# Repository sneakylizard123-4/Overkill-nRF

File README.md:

# Overkill nRF Board

A modular RF communication board designed for the **Overkill system**, built around the **nRF24L01+ radio module** instead of a bare RF IC + Amplifier. This makes the design easier to assemble, debug, and iterate while keeping it fully modular inside the Overkill ecosystem.

---

## Overview

The Overkill nRF Board handles wireless communication for the system using **nRF24L01+ modules**.

It is designed to be:

- Easy to assemble (no RF IC routing complexity)
- Modular (plugs into Overkill ecosystem)
- Hackable (all signals exposed)
- Repairable (no fine-pitch RF ICs)
- Hand-solderable (mostly 0805 components)

### Operating Modes

- **Standalone mode** → acts like a standard nRF24 breakout module
- **Integrated mode** → RF subsystem inside Overkill system

---

## Why

- Most off-the-shelf nRF24 setups are either too barebones or too messy to integrate into real projects. Debugging is hard, power handling is often ignored, and the RF design is usually not optimized for real-world use.
- This board is designed to be a **usable, hackable, and modular RF subsystem** that can be easily integrated into the Overkill system or used standalone for RF experimentation.

---

## Key Changes from Previous Revision

- Removed discrete nRF24 RF IC design
- Switched to **nRF24L01+ module-based design**
- Simplified RF routing significantly
- Improved reliability and build speed
- Reduced RF design complexity

---

## Hardware

### Radio

- nRF24L01+ module (SPI interface)
- Optional PA+LNA module support (with proper power handling)

### Components

- Mostly **0805 footprint components**
  - Easier soldering
  - Better availability
  - More forgiving for hand assembly

### Interface

Connection to Overkill system via **JST-PH connector**:

- 3.3V power
- Data signals

---

## Design Philosophy

This board prioritizes:

- Simplicity over compact size
- Modularity over integration
- Debuggability over RF perfection

The goal is fast iteration for RF experimentation inside the Overkill platform.

---

## Power Notes

- Requires stable **3.3V supply** or **USB power** with proper regulation
- nRF24 modules are 5V tolerant, but the esp32 is not, so 3.3V is used for the logic part of the board
- Add decoupling capacitors close to module
- PA+LNA modules may require higher current bursts during transmission, so ensure power supply can handle it

---

## PCB Design Notes

- Designed around **0805 components**
- Maintain solid ground plane under RF section
- Keep antenna area free of copper and components
- use external antennas if possible for better performance

---

## Images

All pictures and screenshots should be in the `images/` folder.

### PCB Layout

---

### 3D Renders

Top-side render (ray-traced KiCad):

Bottom-side render (ray-traced KiCad):

---

### Schematics

schematic sheet 1:

schematic sheet 2:

---

### Manufacturing / Sourcing

AliExpress cart:

LCSC sourcing carts:

JLCPCB cart:

or maybe PCBWay if they sponsor this project too!

---

### Zine Page

## System Integration

The board connects into the Overkill system via JST-PH and is designed to interface with:

- Core controller board (SPI master)
- Power distribution board
- Other modular subsystems

Other parts of the system are being developed separately.

---

## Assembly and Programming

1. Start with passives
   - Solder resistors and capacitors first
   - Double-check values and placements
2. Power section
   - Assemble regulator and power filtering stage
   - Verify 3.3V rail before adding ICs
3. MCU and logic components
   - Solder ESP32 and other chips
   - Inspect for shorts between pins
4. nRF24 module
   - Carefully align pins
   - ensure solid ground connection
5. LEDs and indicators
   - Add status LEDs if desired
   - Match polarity correctly
   - Confirm resistor values for current limiting
6. Final inspection
   - Continuity check all power rails
   - Inspect RF sections for solder bridges

---

## How to Use

1. Powering the board
   - Connect USB power or 3.3V supply to the JST-PH connector
   - Ensure power supply can provide sufficient current for nRF24 module, especially if using PA+LNA version
2. Programming the ESP32
   - Use PlatformIO or Arduino IDE to flash firmware
   - Connect to the board via USB or UART for debugging
3. Integrating with Overkill system
   - Connect the board to the core controller via JST-PH
   - Use SPI interface to communicate with the nRF24 module
   - Test RF communication with other nRF24 devices

---

## Bill of Materials (BOM)

A full BOM is included in the repository.
see [bom.csv](bom/bom.csv) for details.

It includes:

- Component references
- Values / part numbers
- Quantities
- LCSC number
- Where to get them (AliExpress, LCSC, etc.)

---

## Repository Structure

- bom/ - Bill of Materials (BOM) files
- blender/ - 3D models and renders
- cad/ - STEP files
- firmware/ - code for project (platformio)
- images/ - pictures and screenshots
- kicad/ - KiCad project files
- zine/ - zine page for hack club

---

## Status

- Breadboard Prototype complete
- PCB routed in KiCad
- 3D assembly done
- Ready for fabrication

---

## Notes

This revision prioritizes usability and fast iteration over RF optimization complexity. The goal is to make RF experimentation inside the Overkill system fast, modular, and actually enjoyable to play with.

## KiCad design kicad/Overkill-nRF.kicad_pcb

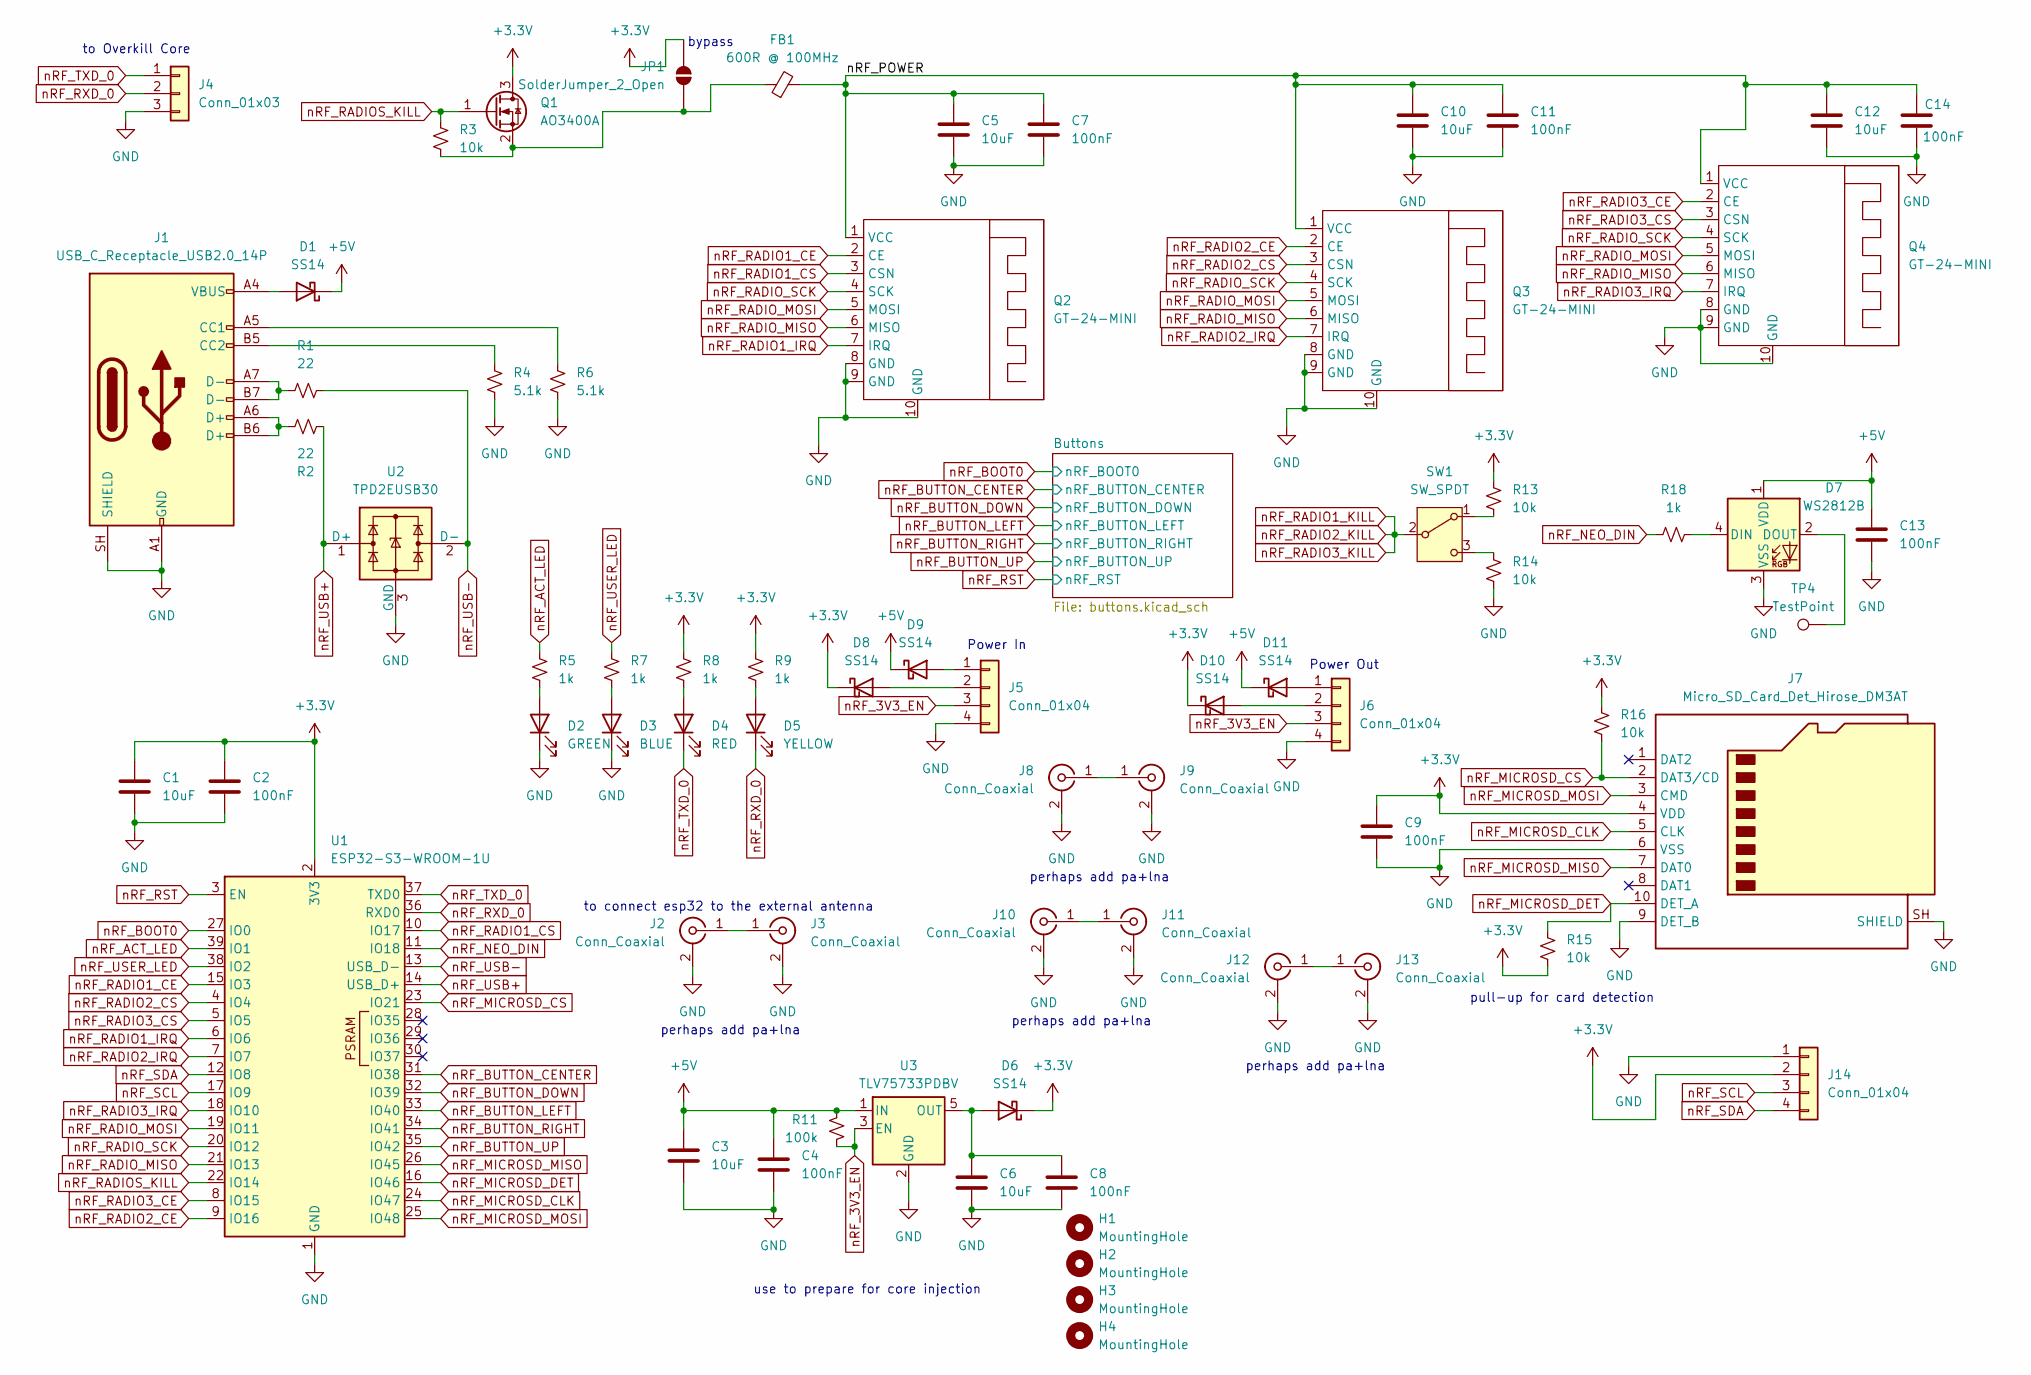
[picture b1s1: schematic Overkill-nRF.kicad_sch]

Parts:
C1, C3, C5, C6, C10, C12: 10uF; C_0805_2012Metric
C2, C4, C7, C8, C9, C11, C13, C14: 100nF; C_0805_2012Metric
D1, D6, D8, D9, D10, D11: SS14; D_SMA
D2: GREEN; LED_0805_2012Metric
D3: BLUE; LED_0805_2012Metric
D4: RED; LED_0805_2012Metric
D5: YELLOW; LED_0805_2012Metric
D7: WS2812B; LED_WS2812B_PLCC4_5.0x5.0mm_P3.2mm
FB1: 600R @ 100MHz; L_0805_2012Metric
H1, H2, H3, H4: MountingHole; MountingHole_3.2mm_M3
J1: USB_C_Receptacle_USB2.0_14P; USB_C_Receptacle_HRO_TYPE-C-31-M-12
J2, J8, J10, J12: Conn_Coaxial; U.FL_Molex_MCRF_73412-0110_Vertical
J3, J9, J11, J13: Conn_Coaxial; SMA_Amphenol_132289_EdgeMount
J4: Conn_01x03; JST_PH_S3B-PH-K_1x03_P2.00mm_Horizontal
J5, J6: Conn_01x04; JST_PH_S4B-PH-K_1x04_P2.00mm_Horizontal
J7: Micro_SD_Card_Det_Hirose_DM3AT; microSD_HC_Molex_104031-0811
J14: Conn_01x04; PinSocket_1x04_P2.54mm_Vertical
JP1: SolderJumper_2_Open; SolderJumper-2_P1.3mm_Open_RoundedPad1.0x1.5mm
Q1: AO3400A; SOT-23
Q2, Q3, Q4: GT-24-MINI; nRF24L01-GT24_Breakout
R1, R2: 22; R_0805_2012Metric
R3, R13, R14, R15, R16: 10k; R_0805_2012Metric
R4, R6: 5.1k; R_0805_2012Metric
R5, R7, R8, R9, R18: 1k; R_0805_2012Metric
R11: 100k; R_0805_2012Metric
SW1: SW_SPDT; SW_SPDT_CK_JS102011SAQN
TP4: TestPoint; TestPoint_Pad_D1.5mm
U1: ESP32-S3-WROOM-1U
U2: TPD2EUSB30; Texas_DRT-3
U3: TLV75733PDBV; SOT-23-5

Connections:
+3.3V: C1.1, C2.1, C9.1, D6.1 (K), D8.1 (K), D10.1 (K), J7.4 (VDD), J14.2, JP1.2 (B), Q1.3 (D), R8.1, R9.1, R13.1, R15.2, R16.1, U1.2 (3V3); also elsewhere on the board
+5V: C3.1, C4.1, C13.1, D1.1 (K), D7.1 (VDD), D9.1 (K), D11.1 (K), R11.1, U3.1 (IN)
/nRF_POWER: C5.1, C7.1, C10.1, C11.1, C12.1, C14.1, FB1.2, Q2.1 (VCC), Q3.1 (VCC), Q4.1 (VCC)
GND: C1.2, C2.2, C3.2, C4.2, C5.2, C6.2, C7.2, C8.2, C9.2, C10.2, C11.2, C12.2, C13.2, C14.2, D2.1 (K), D3.1 (K), D7.3 (VSS), J1.A1 (GND), J1.A12 (GND), J1.B1 (GND), J1.B12 (GND), J1.SH (SHIELD), J2.2 (Ext), J3.2 (Ext), J4.3, J5.4, J6.4, J7.6 (VSS), J7.9 (DET_B), J7.SH (SHIELD), J8.2 (Ext), J9.2 (Ext), J10.2 (Ext), J11.2 (Ext), J12.2 (Ext), J13.2 (Ext), J14.1, Q2.8 (GND), Q2.9 (GND), Q2.10 (GND), Q3.8 (GND), Q3.9 (GND), Q3.10 (GND), Q4.8 (GND), Q4.9 (GND), Q4.10 (GND), R4.2, R6.2, R14.2, U1.1 (GND), U1.40 (GND), U1.41 (GND), U2.3 (GND), U3.2 (GND); also elsewhere on the board
unnamed: D1.2 (A), J1.A4 (VBUS), J1.A9 (VBUS), J1.B4 (VBUS), J1.B9 (VBUS)
unnamed: D2.2 (A), R5.2
unnamed: D3.2 (A), R7.2
unnamed: D4.2 (A), R8.2
unnamed: D5.2 (A), R9.2
unnamed: C6.1, C8.1, D6.2 (A), U3.5 (OUT)
unnamed: D7.4 (DIN), R18.2
unnamed: D7.2 (DOUT), TP4.1 (1_1)
unnamed: D8.2 (A), J5.2
unnamed: D9.2 (A), J5.1
unnamed: D10.2 (A), J6.2
unnamed: D11.2 (A), J6.1
unnamed: J1.A5 (CC1), R6.1
unnamed: J1.B5 (CC2), R4.1
unnamed: J1.A6 (D+), J1.B6 (D+), R2.2
unnamed: J1.A7 (D-), J1.B7 (D-), R1.1
unnamed: J2.1 (In), J3.1 (In)
unnamed: J8.1 (In), J9.1 (In)
unnamed: J10.1 (In), J11.1 (In)
unnamed: J12.1 (In), J13.1 (In)
unnamed: FB1.1, JP1.1 (A), Q1.2 (S), R3.2
unnamed: R13.2, SW1.1 (A)
unnamed: R14.1, SW1.3 (C)
nRF_3V3_EN: J5.3, J6.3, R11.2, U3.3 (EN)
nRF_ACT_LED: R5.1, U1.39 (IO1)
nRF_BOOT0: U1.27 (IO0); also elsewhere on the board
nRF_BUTTON_CENTER: U1.31 (IO38); also elsewhere on the board
nRF_BUTTON_DOWN: U1.32 (IO39); also elsewhere on the board
nRF_BUTTON_LEFT: U1.33 (IO40); also elsewhere on the board
nRF_BUTTON_RIGHT: U1.34 (IO41); also elsewhere on the board
nRF_BUTTON_UP: U1.35 (IO42); also elsewhere on the board
nRF_MICROSD_CLK: J7.5 (CLK), U1.24 (IO47)
nRF_MICROSD_CS: J7.2 (DAT3/CD), R16.2, U1.23 (IO21)
nRF_MICROSD_DET: J7.10 (DET_A), R15.1, U1.16 (IO46)
nRF_MICROSD_MISO: J7.7 (DAT0), U1.26 (IO45)
nRF_MICROSD_MOSI: J7.3 (CMD), U1.25 (IO48)
nRF_NEO_DIN: R18.1, U1.11 (IO18)
nRF_RADIO1_CE: Q2.2 (CE), U1.15 (IO3)
nRF_RADIO1_CS: Q2.3 (CSN), U1.10 (IO17)
nRF_RADIO1_IRQ: Q2.7 (IRQ), U1.6 (IO6)
nRF_RADIO1_KILL: SW1.2 (B)
nRF_RADIO2_CE: Q3.2 (CE), U1.9 (IO16)
nRF_RADIO2_CS: Q3.3 (CSN), U1.4 (IO4)
nRF_RADIO2_IRQ: Q3.7 (IRQ), U1.7 (IO7)
nRF_RADIO3_CE: Q4.2 (CE), U1.8 (IO15)
nRF_RADIO3_CS: Q4.3 (CSN), U1.5 (IO5)
nRF_RADIO3_IRQ: Q4.7 (IRQ), U1.18 (IO10)
nRF_RADIOS_KILL: Q1.1 (G), R3.1, U1.22 (IO14)
nRF_RADIO_MISO: Q2.6 (MISO), Q3.6 (MISO), Q4.6 (MISO), U1.21 (IO13)
nRF_RADIO_MOSI: Q2.5 (MOSI), Q3.5 (MOSI), Q4.5 (MOSI), U1.19 (IO11)
nRF_RADIO_SCK: Q2.4 (SCK), Q3.4 (SCK), Q4.4 (SCK), U1.20 (IO12)
nRF_RST: U1.3 (EN); also elsewhere on the board
nRF_RXD_0: D5.1 (K), J4.2, U1.36 (RXD0)
nRF_SCL: J14.3, U1.17 (IO9)
nRF_SDA: J14.4, U1.12 (IO8)
nRF_TXD_0: D4.1 (K), J4.1, U1.37 (TXD0)
nRF_USB+: R2.1, U1.14 (USB_D+), U2.1 (D+)
nRF_USB-: R1.2, U1.13 (USB_D-), U2.2 (D-)
nRF_USER_LED: R7.1, U1.38 (IO2)

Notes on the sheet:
pull-up for card detection
perhaps add pa+lna
to connect esp32 to the external antenna
bypass
Power In
Power Out
to Overkill Core
use to prepare for core injection

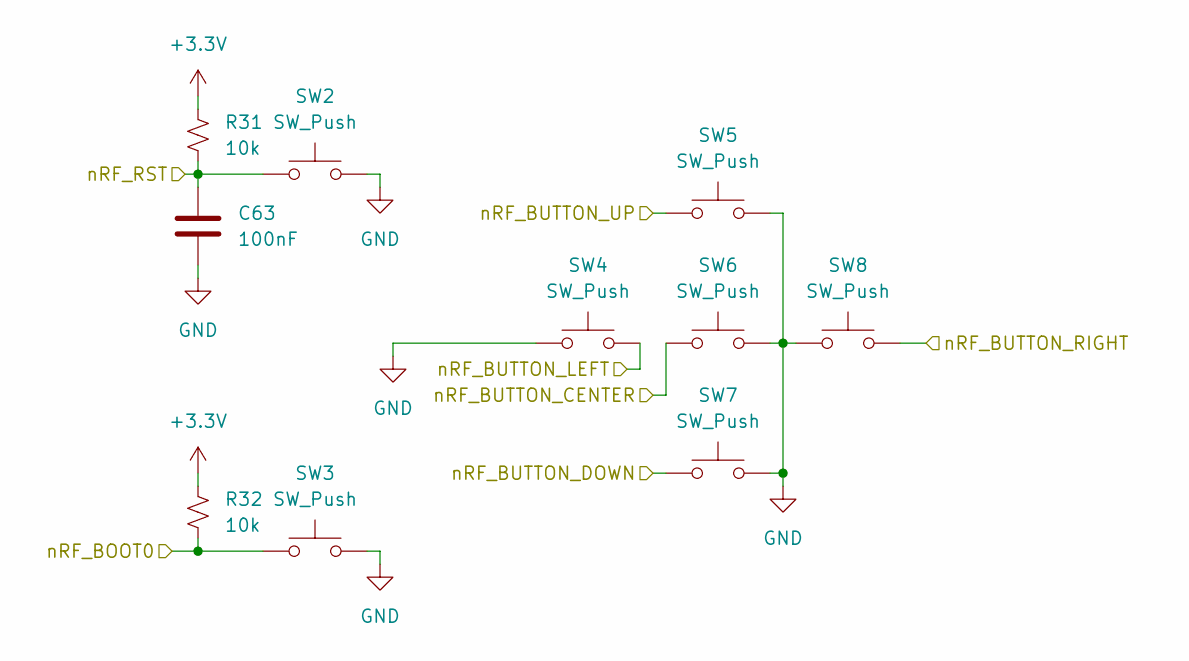
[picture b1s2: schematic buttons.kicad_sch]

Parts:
C63: 100nF; C_0805_2012Metric
R31, R32: 10k; R_0805_2012Metric
SW2, SW3: SW_Push; SW_SPST_B3U-3000P
SW4, SW5, SW6, SW7, SW8: SW_Push; SW_SPST_PTS647_Sx38

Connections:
+3.3V: R31.1, R32.1; also elsewhere on the board
GND: C63.2, SW2.2, SW3.2, SW4.1, SW5.2, SW6.2, SW7.2, SW8.1; also elsewhere on the board
nRF_BOOT0: R32.2, SW3.1; also elsewhere on the board
nRF_BUTTON_CENTER: SW6.1; also elsewhere on the board
nRF_BUTTON_DOWN: SW7.1; also elsewhere on the board
nRF_BUTTON_LEFT: SW4.2; also elsewhere on the board
nRF_BUTTON_RIGHT: SW8.2; also elsewhere on the board
nRF_BUTTON_UP: SW5.1; also elsewhere on the board
nRF_RST: C63.1, R31.2, SW2.1; also elsewhere on the board

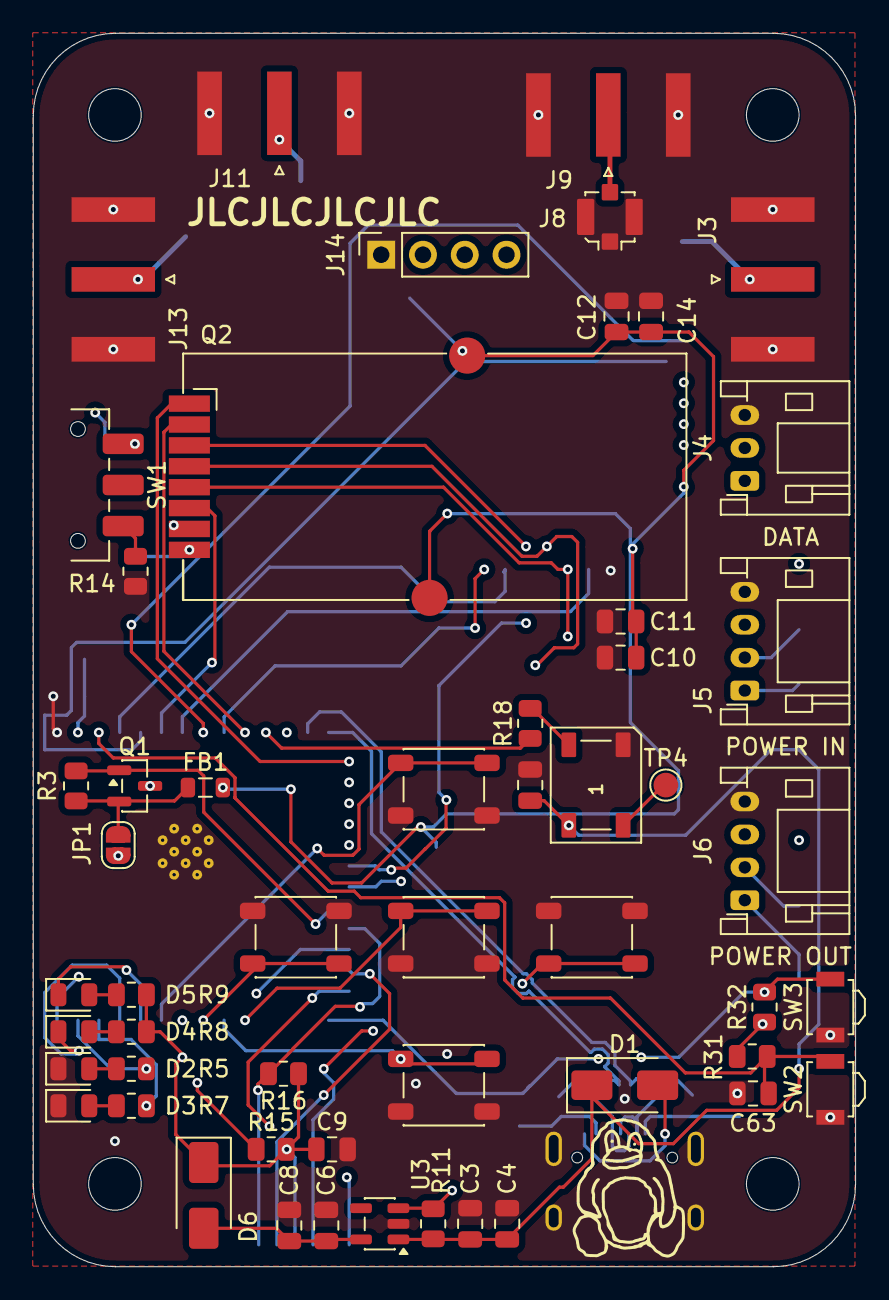
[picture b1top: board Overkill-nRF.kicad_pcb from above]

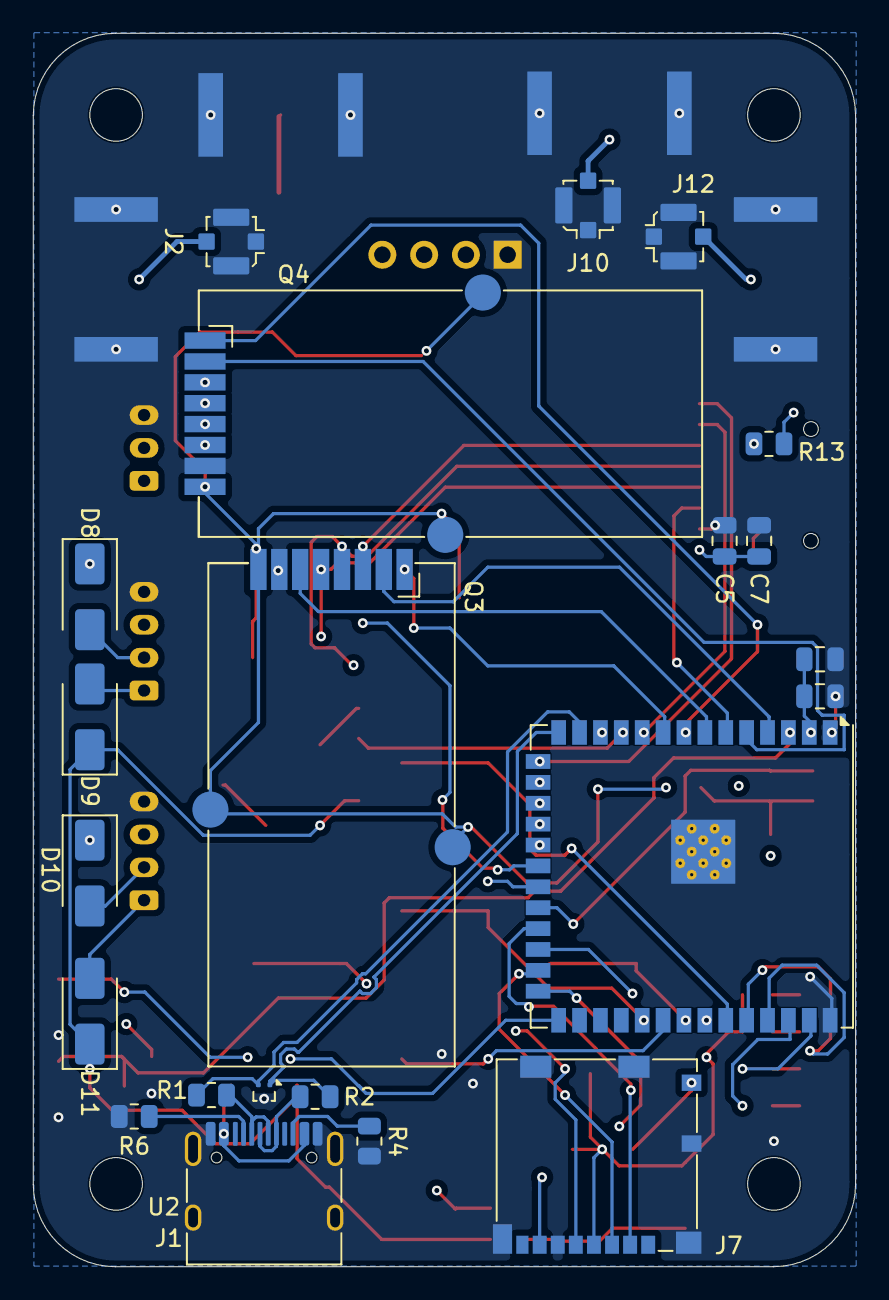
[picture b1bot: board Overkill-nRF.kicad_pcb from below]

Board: 4 copper layers, 50.0 x 75.0 mm, 79 parts (22 on the bottom side), 62 nets.

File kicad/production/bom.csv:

Designator,Footprint,Quantity,Value,LCSC Part #
"C1, C10, C12, C3, C5, C6",0805,6,10uF,
"C11, C13, C14, C2, C4, C63, C7, C8, C9",0805,9,100nF,
"D1, D10, D11, D6, D8, D9",D_SMA,6,SS14,
D2,0805,1,GREEN,
D3,0805,1,BLUE,
D4,0805,1,RED,
D5,0805,1,YELLOW,
D7,LED_WS2812B_PLCC4_5.0x5.0mm_P3.2mm,1,WS2812B,
FB1,0805,1,600R @ 100MHz,
J1,USB_C_Receptacle_HRO_TYPE-C-31-M-12,1,USB_C_Receptacle_USB2.0_14P,
"J10, J12, J2, J8",U.FL_Molex_MCRF_73412-0110_Vertical,4,Conn_Coaxial,
"J11, J13, J3, J9",SMA_Amphenol_132289_EdgeMount,4,Conn_Coaxial,
J14,PinSocket_1x04_P2.54mm_Vertical,1,Conn_01x04,
J4,JST_PH_S3B-PH-K_1x03_P2.00mm_Horizontal,1,Conn_01x03,
"J5, J6",JST_PH_S4B-PH-K_1x04_P2.00mm_Horizontal,2,Conn_01x04,
J7,microSD_HC_Molex_104031-0811,1,Micro_SD_Card_Det_Hirose_DM3AT,
Q1,SOT-23,1,AO3400A,
"Q2, Q3, Q4",nRF24L01-GT24_Breakout,3,GT-24-MINI,
"R1, R2",0805,2,22,
R11,0805,1,100k,
"R13, R14, R15, R16, R3, R31, R32",0805,7,10k,
"R18, R5, R7, R8, R9",0805,5,1k,
"R4, R6",0805,2,5.1k,
SW1,SW_SPDT_CK_JS102011SAQN,1,SW_SPDT,
"SW2, SW3",SW_SPST_B3U-3000P,2,SW_Push,
"SW4, SW5, SW6, SW7, SW8",SW_SPST_PTS647_Sx38,5,SW_Push,
TP4,TestPoint_Pad_D1.5mm,1,TestPoint,
U1,ESP32-S3-WROOM-1U,1,ESP32-S3-WROOM-1U,
U2,Texas_DRT-3,1,TPD2EUSB30,
U3,SOT-23-5,1,TLV75733PDBV,

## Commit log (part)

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2026-04-19 add images and remove files
2026-04-19 add cad
2026-04-19 add blender file
2026-04-19 blendin
2026-04-19 add readme
2026-04-19 add firmware and bom
2026-04-19 align bom csv
2026-04-19 format with trunk
2026-04-19 rename images and integrate into readme
2026-04-19 polish readme
2026-04-19 add jlcpcb to images
2026-04-19 fix readme
2026-04-19 move to bom file
2026-04-19 update bom
2026-04-19 add zine
2026-04-19 add freecad
2026-04-19 add gitignore
2026-04-19 update boms
2026-04-19 add flashing to readme
2026-04-19 align bom
2026-04-19 remove test
2026-04-19 update cost
2026-04-19 add bom
2026-04-20 clean
2026-04-20 remove unnecessary bom
2026-04-20 fix bom
2026-04-20 test bom files
2026-04-20 update bom section
2026-04-20 update gitignore
2026-04-20 move bom
2026-04-20 bom try again
2026-04-20 add assembly
2026-04-20 fix type
2026-04-20 add readme how to use
2026-04-26 upate zine
2026-05-03 update firmware
